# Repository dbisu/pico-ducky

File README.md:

<h1 align="center">pico-ducky</h1>

<div align="center">
  <strong>Make a cheap but powerful USB Rubber Ducky with a Raspberry Pi Pico</strong>
</div>

<br />

<div align="center">

</div>

<br />

## Quick Start Guide
Install and have your USB Rubber Ducky working in less than 5 minutes.

1. Download the latest release from the [Releases](https://github.com/dbisu/pico-ducky/releases) page.

2. Plug the device into a USB port while holding the boot button. It will show up as a removable media device named RPI-RP2.

3. Install CircutlPython on the Pico or Pico W

If using a Pico board:

Copy the adafruit-circuitpython-raspberry_pi_pico-en_US-9.2.1.uf2 file to the root of the Pico (RPI-RP2). The device will reboot and after a second or so, it will reconnect as CIRCUITPY.

If using a Pico W board:

Copy the adafruit-circuitpython-raspberry_pi_pico_w-en_US-9.2.1.uf2 file to the root of the Pico (RPI-RP2). The device will reboot and after a second or so, it will reconnect as CIRCUITPY.  

If using a Pico 2 board:

Copy the adafruit-circuitpython-raspberry_pi_pico2-en_US-9.2.1.uf2 file to the root of the Pico (RPI-RP2). The device will reboot and after a second or so, it will reconnect as CIRCUITPY.

If using a Pico 2W board:

Copy the adafruit-circuitpython-raspberry_pi_pico2_w-en_US-9.2.1.uf2 file to the root of the Pico (RPI-RP2). The device will reboot and after a second or so, it will reconnect as CIRCUITPY.

4. Copy the lib folder to the root of the CIRCUITPY

5. Copy *.py to the root of the CIRCUITPY

6. Follow the instructions in README.md to enter setup mode

7. Copy your payload as payload.dd to the root of the CIRCUITPY

8. Unplug the device from the USB port and remove the setup jumper.

Enjoy your Pico-Ducky.

## Setup mode

To edit the payload, enter setup mode by connecting the pin 1 (`GP0`) to pin 3 (`GND`), this will stop the pico-ducky from injecting the payload in your own machine.
The easiest way to do so is by using a jumper wire between those pins as seen bellow.

## USB enable/disable mode

If you need the pico-ducky to not show up as a USB mass storage device for stealth, follow these instructions.  
- Enter setup mode.    
- Copy your payload script to the pico-ducky.  
- Disconnect the pico from your host PC.
- Connect a jumper wire between pin 18 (`GND`) and pin 20 (`GPIO15`).  
This will prevent the pico-ducky from showing up as a USB drive when plugged into the target computer.  
- Remove the jumper and reconnect to your PC to reprogram.  

Pico: The default mode is USB mass storage enabled.   
Pico W: The default mode is USB mass storage **disabled**  

-----

# Full Install Instructions

Install and have your USB Rubber Ducky working in less than 5 minutes.

1. Clone the repo to get a local copy of the files. `git clone https://github.com/dbisu/pico-ducky.git`

2. Download [CircuitPython for the Raspberry Pi Pico](https://circuitpython.org/board/raspberry_pi_pico/). *Updated to 9.2.1  
   Download [CircuitPython for the Raspberry Pi Pico W](https://circuitpython.org/board/raspberry_pi_pico_w/). *Updated to 9.2.1
   Download [CircuitPython for the Raspberry Pi Pico 2](https://circuitpython.org/board/raspberry_pi_pico2/). *Updated to 9.2.1  
   Download [CircuitPython for the Raspberry Pi Pico 2W](https://circuitpython.org/board/raspberry_pi_pico2_w/). *Updated to 9.2.1

3. Plug the device into a USB port while holding the boot button. It will show up as a removable media device named `RPI-RP2`.

4. Copy the downloaded `.uf2` file to the root of the Pico (`RPI-RP2`). The device will reboot and after a second or so, it will reconnect as `CIRCUITPY`.

5. Download `adafruit-circuitpython-bundle-9.x-mpy-YYYYMMDD.zip` [here](https://github.com/adafruit/Adafruit_CircuitPython_Bundle/releases/latest) and extract it outside the device.

6. Navigate to `lib` in the recently extracted folder and copy `adafruit_hid` to the `lib` folder on your Raspberry Pi Pico.

7. Copy `adafruit_debouncer.mpy` and `adafruit_ticks.mpy` to the `lib` folder on your Raspberry Pi Pico.

8. Copy `asyncio` to the `lib` folder on your Pico.

9. Copy `adafruit_wsgi` to the `lib` folder on your Pico.

10. Copy `boot.py` from your clone to the root of your Pico.

11. Copy `duckyinpython.py`, `code.py`, `webapp.py`, `wsgiserver.py` to the root folder of the Pico.

12. *For Pico W Only* Create the file `secrets.py` in the root of the Pico W. This contains the AP name and password to be created by the Pico W.  
`secrets = { 'ssid' : "BadAPName", 'password' : "badpassword" }`

13. Find a script [here](https://github.com/hak5/usbrubberducky-payloads) or [create your own one using Ducky Script](https://docs.hak5.org/hak5-usb-rubber-ducky/ducky-script-basics/hello-world) and save it as `payload.dd` in the Pico. Currently, pico-ducky only supports DuckyScript 1.0, and some of 3.0.

14. Be careful, if your device isn't in [setup mode](#setup-mode), the device will reboot and after half a second, the script will run.

15. **Please note:** by default Pico W will not show as a USB drive

### Pico W Web Service
The Pico W AP defaults to ip address `192.168.4.1`.  You should be able to find the webservice at `http://192.168.4.1:80`  

The following endpoints are available on the webservice:
```
/
/new
/ducky
/edit/<filename>
/write/<filename>
/run/<filename>
```

API endpoints
```
/api/run/<filenumber>
```

## Setup mode

To edit the payload, enter setup mode by connecting the pin 1 (`GP0`) to pin 3 (`GND`), this will stop the pico-ducky from injecting the payload in your own machine.
The easiest way to do so is by using a jumper wire between those pins as seen bellow.

## USB enable/disable mode

If you need the pico-ducky to not show up as a USB mass storage device for stealth, follow these instructions.  
- Enter setup mode.    
- Copy your payload script to the pico-ducky.  
- Disconnect the pico from your host PC.
- Connect a jumper wire between pin 18 (`GND`) and pin 20 (`GPIO15`).  
This will prevent the pico-ducky from showing up as a USB drive when plugged into the target computer.  
- Remove the jumper and reconnect to your PC to reprogram.  

Pico: The default mode is USB mass storage enabled.   
Pico W: The default mode is USB mass storage **disabled**  

## Multiple payloads

Multiple payloads can be stored on the Pico and Pico W.  
To select a payload, ground one of these pins:
- GP4 - payload.dd
- GP5 - payload2.dd
- GP10 - payload3.dd
- GP11 - payload4.dd

## Changing Keyboard Layouts

Copied from [Neradoc/Circuitpython_Keyboard_Layouts](https://github.com/Neradoc/Circuitpython_Keyboard_Layouts/blob/main/PICODUCKY.md)  

#### How to use one of these layouts with the pico-ducky repository.

**Go to the [latest release page](https://github.com/Neradoc/Circuitpython_Keyboard_Layouts/releases/latest), look if your language is in the list.**

#### If your language/layout is in the bundle

Download the `py` zip, named `circuitpython-keyboard-layouts-py-XXXXXXXX.zip`

**NOTE: You can use the mpy version targetting the version of Circuitpython that is on the device, but on Raspberry Pi Pico you don't need it - they only reduce file size and memory use on load, which the pico has plenty of.**

#### If your language/layout is not in the bundle

Try the online generator, it should get you a zip file with the bundles for yout language

https://www.neradoc.me/layouts/

#### Now you have a zip file

#### Find your language/layout in the lib directory

For a language `LANG`, copy the following files from the zip's `lib` folder to the `lib` directory of the board.  
**DO NOT** modify the adafruit_hid directory. Your files go directly in `lib`.  
**DO NOT** change the names or extensions of the files. Just pick the right ones.  
Replace `LANG` with the letters for your language of choice.

- `keyboard_layout_win_LANG.py`
- `keycode_win_LANG.py`

Don't forget to get [the adafruit_hid library](https://github.com/adafruit/Adafruit_CircuitPython_HID/releases/latest).

This is what it should look like **if your language is French for example**.

#### Modify the pico-ducky code to use your language file:

At the start of the file comment out these lines:

```py
from adafruit_hid.keyboard_layout_us import KeyboardLayoutUS as KeyboardLayout
from adafruit_hid.keycode import Keycode
```

Uncomment these lines:  
*Replace `LANG` with the letters for your language of choice. The name must match the file (without the py or mpy extension).*
```py
from keyboard_layout_win_LANG import KeyboardLayout
from keycode_win_LANG import Keycode
```

##### Example:  Set to German Keyboard (WIN_DE)

```py
from keyboard_layout_win_de import KeyboardLayout
from keycode_win_de import Keycode
```

Copy the files keyboard_layout_win_de.mpy and keycode_win_de.mpy to the /lib folder on the Pico board
```
adafruit_hid/
keyboard_layout_win_de.mpy
keycode_win_de.mpy
```

## Useful links and resources

### How to recover your Pico if it becomes corrupted or doesn't boot.

[Reset Instructions](RESET.md)

### Installation Tool

[ryo-yamada](https://github.com/ryo-yamada) Created a tool to convert a blank RPi Pico to a ducky.  
You can find the tool [here](https://github.com/ryo-yamada/PicoDuckyBuilder)

### Docs

[CircuitPython](https://circuitpython.readthedocs.io/en/6.3.x/README.html)

[CircuitPython HID](https://learn.adafruit.com/circuitpython-essentials/circuitpython-hid-keyboard-and-mouse)

[Ducky Script](https://github.com/hak5darren/USB-Rubber-Ducky/wiki/Duckyscript)

### Video tutorials

[pico-ducky tutorial by **NetworkChuck**](https://www.youtube.com/watch?v=e_f9p-_JWZw)

[USB Rubber Ducky playlist by **Hak5**](https://www.youtube.com/playlist?list=PLW5y1tjAOzI0YaJslcjcI4zKI366tMBYk)

[CircuitPython tutorial on the Raspberry Pi Pico by **DroneBot Workshop**](https://www.youtube.com/watch?v=07vG-_CcDG0)

## Related Projects

[Defcon31-ducky](https://github.com/iot-pwn/defcon31-ducky)  
There are still a few of these available to purchase, US only.

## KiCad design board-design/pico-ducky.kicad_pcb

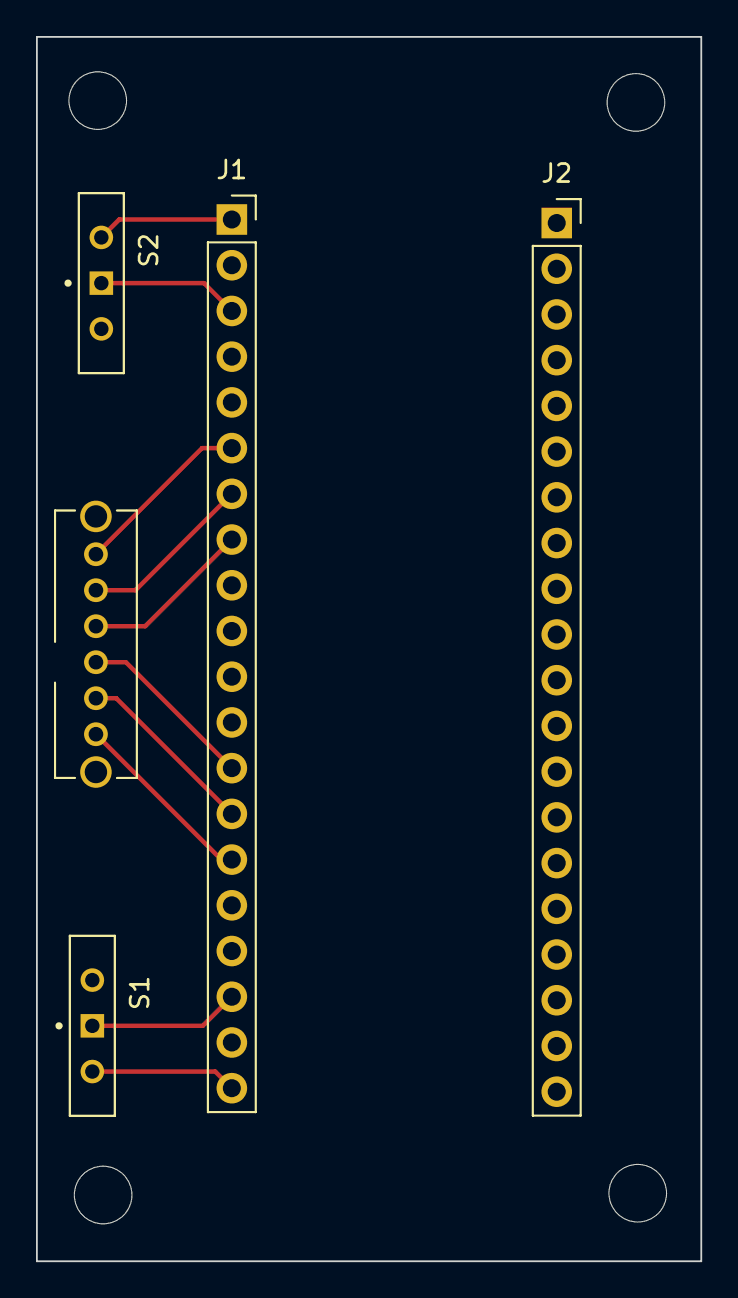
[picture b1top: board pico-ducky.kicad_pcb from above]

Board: 2 copper layers, 36.9 x 68.0 mm, 5 parts (0 on the bottom side), 10 nets.

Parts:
J1, J2: Conn_01x20_Female; PinSocket_1x20_P2.54mm_Vertical
S1, S2: MSS-102545-14A-D; SW_MSS-102545-14A-D
SW3: SK-14D01-G_6; SK-14D01-G 6

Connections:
unnamed: J1.1, S2.2
unnamed: J1.3, S2.1
unnamed: J1.6, SW3.1
unnamed: J1.7, SW3.2
unnamed: J1.8, SW3.3
unnamed: J1.13, SW3.4
unnamed: J1.14, SW3.5
unnamed: J1.15, SW3.6
unnamed: J1.18, S1.1
unnamed: J1.20, S1.3

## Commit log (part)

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2021-02-04 Initial code commit
2021-02-04 Fix docs
2021-06-15 Fixed issue with Windows line endings causing the script to crash
2021-06-16 Better fix for issue 1
2021-08-21 Update README.md documentation
2021-08-21 Add Programming switch (#4)
    * Add support for programming switch
    * Update README.md documentation
2021-08-25 Removed unneeded returns, and changed defaultdelay to global
2021-08-25 Removed unneeded returns, and changed defaultdelay to global (#6)
2021-08-26 update README instructions and formatting add badges and useful resources to README change payload to open notepad and type "Hello World!" in Windows fix comments in duckyinpython.py rename "pics" fo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
2021-08-28 update README instructions and formatting (#9)
    add badges and useful resources to README
    change payload to open notepad and type "Hello World!" in Windows
    fix comments in duckyinpython.py
    rename "pics" folder to "images"
    update setup mode image to a clearer one
2021-09-04 Added function keys. Made programming pin status check more clear. (#14)
2021-09-05 Testing German Keyboard Layout
2021-09-11 Use pass instead of print("")
    I dont know if it helps in performance but the output is more clean
2021-09-12 Updating instructions for adding keyboard layouts
2021-09-17 fix identifying keycodes, and find all keycodes
2021-09-18 don't print a message on empty spaces
2021-09-18 Fixed key parsing to ensure the correct keys are found
2021-09-25 Updated README to CircuitPython 7.0.0
2021-09-25 Updated README to CircuitPython 7.0.0 (#24)
2021-10-03 Added USB enable-disable mode
2021-10-04 Add files
2021-10-06 Added troubleshoot guide and use download release
2021-10-17 Make switching keyboard layouts easier
2021-10-17 fix typos
2021-10-31 Keyboard layouts (#30)
    * Make switching keyboard layouts easier
    * Fix broken image link
    * fix typos
2021-11-06 add LOCALE command
    dynamically switch keyboard layout
2021-11-06 allow repeating imports
2021-11-06 fix: defaultdelay not set correctly
2021-11-06 fix: defaultdelay not set correctly (#34)
2021-11-19 Added license and copyright information clarity (#36)
2021-11-30 Update installation instructions
2021-12-08 [READ EXTENDED DESCRIPTION]
    Changes made:
    1. Removed a few print statements for a bit less cluttering (Makes debugging a bit harder)
    2. Added a PRINT command for writing to console.
    3. Added an IMPORT command for running external ".dd" files.
    4. Added an LED command that toggles the builtin LED.
2021-12-09 Updated the DELETE keycode
2021-12-10 Defaults the USB to stealth mode and disables everything except HID devices.
2021-12-10 Makes the payload update pin match the stealth pin
    Also deleted the random comment
2021-12-10 When typo fixed be like (DEFAULT PAYLOAD RUNS FROM A FOLDER CALLED SCRIPTS)
2021-12-11 Updated to check the DOWN button on boot
2021-12-11 Add dummy payloads
2021-12-11 update Rubber Nugget software
2021-12-11 Fixed typo
2022-01-06 Runs the main program
2022-01-06 replaced with code.py
2022-01-06 Update quick inject feature
2022-01-16 remove second `DELETE`
2022-01-16 remove second `DELETE` (#46)
2022-02-03 bad imports and error handling
2022-02-03 added demo
2022-02-03 deleted unwanted video
2022-02-11 Removed keyboard_layout.py
    `keyboard_layout.py` is now in adafruit_hid (version 5+) and no longer needed.
2022-02-13 Adding support for four position switch to select payloads
2022-02-25 Adding support for four position switch to select payloads (#51)
2022-03-09 saving some memory
2022-03-10 better syntax
2022-03-11 Saving some memory (#55)
    * saving some memory
    * remove print
    * better syntax
    * Update duckyinpython.py
2022-03-18 Disable auto reload when a new payload or code is deployed. Add blinking LED when board is idle, ready for reload or payload is finished running
2022-03-18 Only present as a keyboard and not both keyboard and mouse
2022-03-19 Quick payload deploy test
2022-03-19 Add files via upload
    Updated payloads to .txt instead of .dd
2022-03-19 Upload Test
2022-03-27 Update README.md (#65)
2022-04-03 Add exception handling to file open
2022-04-05 making light pwm
2022-04-05 making light pwm (#68)
2022-04-10 Update README to clarify non-US keyboard instructions
2022-04-10 Update README to clarify non-US keyboard instructions (#70)
2022-06-12 Add link to installation tool
2022-06-12 Update links
2022-06-12 Install tool (#77)
    * Add link to installation tool
    * Update links
2022-08-09 Update boot.py
    Moving "No Storage" pin to GPIO 10 in junction with moving "Setup" pin to GPIO 9 with GND as common in junction with a SPDT micro switch to switch between stealth mode and setup mode. Part 1
2022-08-09 Update duckyinpython.py
    Moving "No Storage" pin to GPIO 10 in junction with moving Setup pin to GPIO 9 with GND as common in junction with a SPDT micro switch to switch between stealth mode and setup mode. Part 2
    Also changed the GPIO of Payload 3 and Payload 4 to GPIO 6 & 7 respectively for those options. (GND sits between 4,5 & 6,7. will use this with a custom SP4T switch)
    Needs Testing.
2022-08-09 Add files via upload
    Update images
2022-08-10 Update duckyinpython.py
    Payload1State actually runs Payload1.dd
    This slide switch has its common pin on the outsides (GND) with the selectors now changed to (GP2-5) as the selections.
    https://www.digikey.com/en/products/detail/apem-inc/SLB1470/1797276
    Can be used later with a thumb switch such as this
    https://www.digikey.com/en/products/detail/omron-electronics-inc-emc-div/A7DP-206-1/368288
    or a rotary DIP switch such as this
2022-08-11 Incorporate Rotary DIP Switch code
    Option to have up to 16 payloads selectable using just 4 GPIO pins.
    Updated Readme.md to refelect instructions.
2022-08-11 Update README.md
    syntax in README.md
2022-08-27 Add button to run scripts
2022-08-29 Add button to run scripts (#92)
2022-09-01 Fix library includes and GPIO names
2022-09-09 remove 'digitalio' import to use 'DigitalInOut' & 'Pull'
2022-09-09 cleanup and naming
2022-09-09 cleanup
2022-09-09 Always select payload to be able to send it with button in setup mode
2022-09-18 Change button monitoring and LED to async tasks
2022-09-18 Change button monitoring and LED to async tasks (#98)
2022-09-19 Add reset instructions
2022-09-27 Clean up instructions
2022-09-27 Fix formatting
2022-09-27 Doc updates (#104)
    * Update instructions to include copying boot.py
    * Clean up instructions
    * Fix formatting
2022-11-19 Refactor code to support Pico W board
2022-11-20 Updates for Pico W support
2022-11-21 Update links for payloads and DuckyScript reference
2022-12-29 Update based on changes in CircuitPython v8.0.0 beta 6
2023-01-02 Add ducky3inpython.py
    This is an interpreter for DuckyScript 3.0 that can handle variables, constants, conditional statements, nested conditional statements, loops, and functions. Almost all of the functionality in `ducky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
    **No advanced features have been added**. This means randomization, holding keys, payload control, jitter, payload hiding, storage activity, lock keys, exfiltration, and extensions have not been adde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
2023-01-16 Updating installation tool repo and user
2023-01-22 css:D
2023-01-30 removed the import
    Should still work on most devices since Open Sans is often integrated, worst case it doesn't use the font
2023-02-11 Updated bundle download to 8.x, fixed a few typos
2023-02-11 Updating documentation for web interface
2023-02-18 Document multiple payload options
2023-02-18 Update copyright dates
2023-02-18 Pico W Support (#137)
    * Refactor code to support Pico W board
    * Updates for Pico W support
    * Update based on changes in CircuitPython v8.0.0 beta 6
    * Updated bundle download to 8.x, fixed a few typos
    * Updating documentation for web interface
    * Update support for CircuitPython 8.0.0, fix many bugs
2023-02-19 fix language support (#140)
2023-02-20 Update webapp.py
    PS: Font will work on most devices (preinstalled), else it doesn't really matter
2023-02-22 adding mouse support, inspired by omg cable
2023-03-26 Add files via upload (#150)
2023-04-17 DOC: typo fix in README.md
    DuckScript -> DuckyScript
2023-04-17 DOC: typo fix in README.md (#172)
    DuckScript -> DuckyScript
2023-04-20 FEAT: Windows detection
2023-04-24 DRAFT: IF condition
2023-04-28 DRAFT: if statement draft 2.0
2023-04-29 DRAFT: 3.0 if statement draft
2023-05-07 Added variables and variable check in if
2023-05-07 Added constants
2023-06-16 Add script for automated installation
    All you have to do is to plug in your Pi Pico W and run the script.
    The script will give instructions if the Pi is not in the right mode.
2023-06-24 Clarify getting latest release
2023-06-30 fixed crashes on one-line scripts, auto .dd
2023-06-30 Additional crash fix
2023-07-14 Fix typo
2023-08-07 Create nothing
2023-08-07 Create 123
2023-08-07 Create 12345
2023-09-17 Refactor script running to support long delays without blocking webservice
2023-09-17 Fix typo (#197)
2023-10-18 Example readme & comment fix
2023-11-21 Adafruit Trinkey QT2040 support
2024-01-17 Add link to defcon31-ducky project
2024-02-13 added new wait_for_button_press functionality
2024-02-24 minor payload changes
2024-02-25 code style changes, add support for lang switching
2024-02-25 revert unsupported changes
2024-02-25 Update example payload [payload0.dd]
2024-03-13 Add debugging instructions
2024-07-02 Add functions, while loops, and vars support
2024-07-06 Add support for nested WHILE loops in function
2024-09-21 Add functions, while loops, and vars support (#264)
    * Add functions, while loops, and vars support
    * Add back REPEAT
    * Add support for nested WHILE loops in function
    ---------
2024-10-03 Adding support for STRINGLN
    STRINGLN in DuckyScript presses ENTER once the string got typed
2024-12-21 Add bundle script
2024-12-21 Add support for Pico2/2W boards
2024-12-21 Update documentation to include Pico2/2W
2024-12-21 Pico2 support (#299)
    * Add support for Pico2/2W boards
    * Update documentation to include Pico2/2W
    * update language support
2024-12-24 Added HOLD and RELEASE
2024-12-24 Update removed unnecessary heldKeys var
2024-12-28 Fixed HOLD being released after key press
2024-12-29 Fix bug importing keyboard layouts (#302)
2024-12-31 added REM_BLOCK, STRING Block, and STRINGLN Block
2024-12-31 LED + INJECT_MOD
2024-12-31 added all randoms
2024-12-31 added stop, restart, reset
2024-12-31 bugfixes and cleanup
2025-01-03 Added duckyScript 3.0 functionality (#300)
    * Added HOLD and RELEASE
    * Update removed unnecessary heldKeys var
    * Fixed HOLD being released after key press
    * added REM_BLOCK, STRING Block, and STRINGLN Block
    * LED + INJECT_MOD
    * add define
2025-01-04 added math to variables as well as the ability to use them in DELAY and PRINT/PRINTLN
2025-01-05 Enable Storage in Setup Mode
    Enabled storage when the setup pin is grounded for wireless devices for ease of configuration
2025-01-16 Fix build script to find the correct keyboard_ lines
2025-01-16 remove power key due to keyboard layout issues (#310)
2025-01-16 Fix build script to find the correct keyboard_ lines (#311)
2025-01-17 Change link to new PicoDuckyBuilder script (#315)
2025-01-17 add comparisons
2025-01-17 Added While loops and Conditional statements
2025-01-18 If and While loops working
2025-01-25 add internal variables
2025-01-26 While loops and conditional statements (#316)
    * added math to variables as well as the ability to use them in DELAY and PRINT/PRINTLN
    * add comparisons
    * fix typo
    * Added While loops and Conditional statements
    * If and While loops working
2025-01-26 remove extra spacing
2025-03-03 Fix evaluating with Booleans
2025-03-03 replaced re with a function (this feature of re is not supported on circutpython)
2025-03-03 Fixed internalVar in expression + allows for +=, *=, etc in variable math
2025-03-04 Fix duplicate lines
2025-03-15 Fix which issue templates are available
2025-03-15 Fix which issue templates are available (#329)
2026-03-18 Fixing asyncio issues in webapp
2026-04-11 Fix typo in while loop string message

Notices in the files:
parts and their libraries:
Copyright 2021 Accelerated Designs. All rights reserved.
